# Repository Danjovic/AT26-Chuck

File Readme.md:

# AT-26 Chuck
This project allow the use of a Wii Nunchuck for playing games with Atari 2600 and other video-games with compatible joystick port (like ZX Spectrum w/ Kempston).

The heart of the circuit is a PIC microcontroller that converts I2C data from Wii Nunchuck. into pressing of switches on the Atari Joystick.

The device can be programmed into several modes of operation, with or without the accelerometers and auto-fire. The configuration is stored in EEPROM.

All components are through hole and the board can be easily built at home.

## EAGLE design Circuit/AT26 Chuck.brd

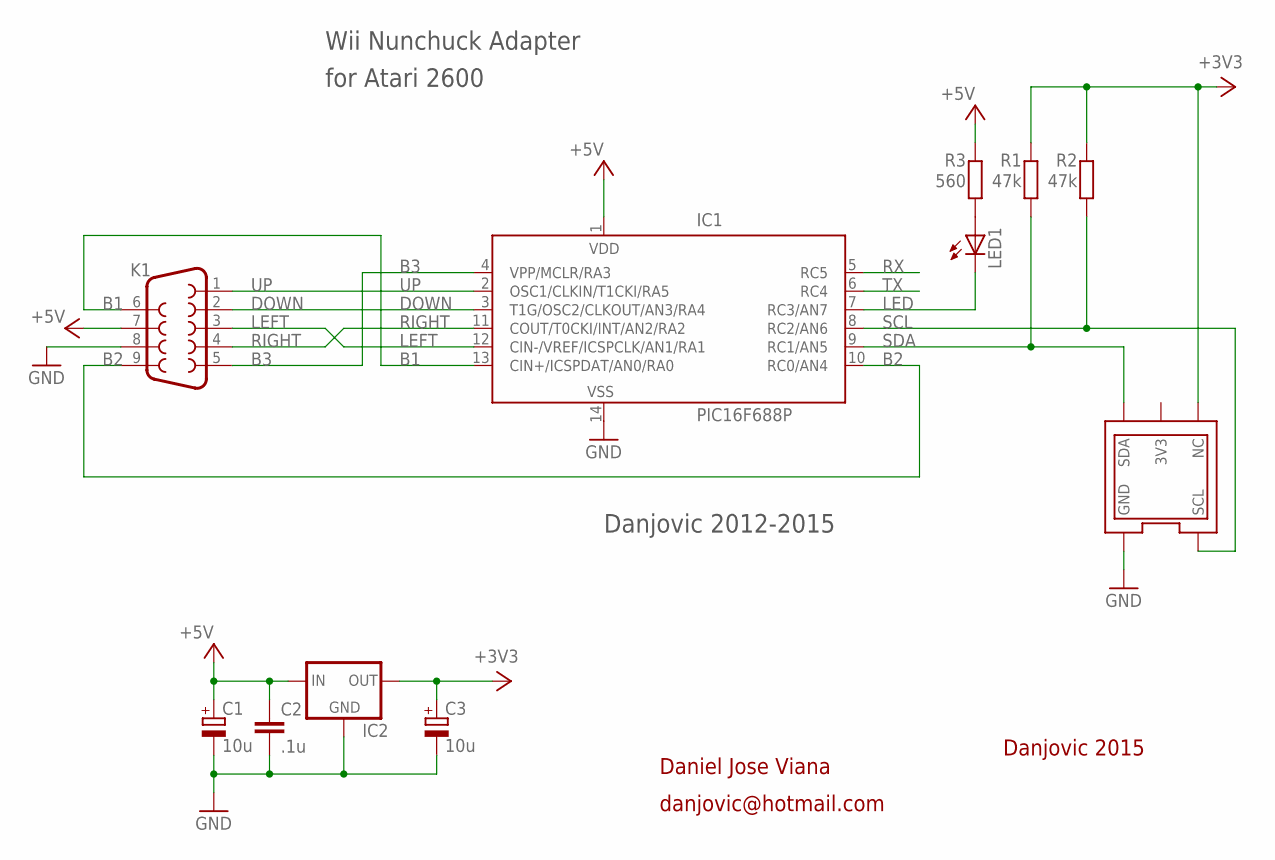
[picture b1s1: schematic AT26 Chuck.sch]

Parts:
C1, C3: 10u; E2,5-5
C2: .1u; C025-024X044L
IC1: PIC16F688P; DIL14
IC2: 78LXX78LXX_L; 78LXX_L
K1: F09D
LED1: LED3MM
R1, R2: 47k; 0204V
R3: 560; 0204V
U$1: NUNCHUCK; NUNCHUCK_SLOT

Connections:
+3V3: C3.+, IC2.OUT, R1.2, R2.2, U$1.NC
+5V: C1.+, C2.1, IC1.1 (VDD), IC2.IN, K1.7, R3.2
B1: IC1.13 (CIN+/ICSPDAT/AN0/RA0), K1.6
B2: IC1.10 (RC0/AN4), K1.9
B3: IC1.4 (VPP/MCLR/RA3), K1.5
DOWN: IC1.3 (T1G/OSC2/CLKOUT/AN3/RA4), K1.2
GND: C1.-, C2.2, C3.-, IC1.14 (VSS), IC2.GND, K1.8, U$1.GND
LED: IC1.7 (RC3/AN7), LED1.K (C)
LEFT: IC1.12 (CIN-/VREF/ICSPCLK/AN1/RA1), K1.3
unnamed: LED1.A, R3.1
RIGHT: IC1.11 (COUT/T0CKI/INT/AN2/RA2), K1.4
RX: IC1.5 (RC5)
SCL: IC1.8 (RC2/AN6), R2.1, U$1.SCL
SDA: IC1.9 (RC1/AN5), R1.1, U$1.SDA
TX: IC1.6 (RC4)
UP: IC1.2 (OSC1/CLKIN/T1CKI/RA5), K1.1

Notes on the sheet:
Danjovic 2015
Daniel Jose Viana
danjovic@hotmail.com
Danjovic 2012-2015
for Atari 2600
Wii Nunchuck Adapter

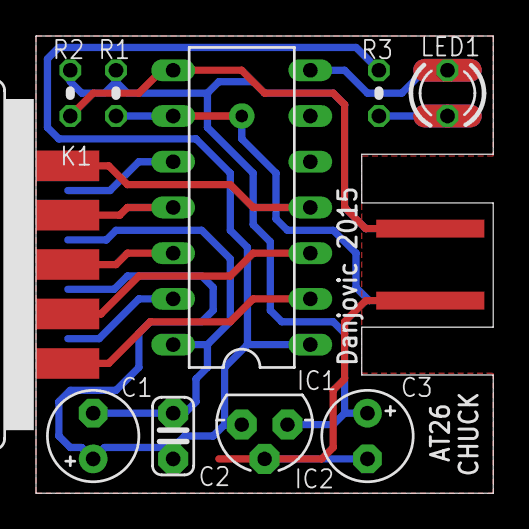
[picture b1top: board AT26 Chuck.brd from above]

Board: 2 copper layers, 25.4 x 25.4 mm, 11 parts (1 on the bottom side), 14 nets.

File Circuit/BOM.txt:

# AT26-Chuck Bill of Materials

IC1   - PIC16F688, DIP14 Package PIC microcontroller 4K Flash, 14 pins
IC2   - 78L33 Voltage Regulator, TO92 package
LED1  - 3mm LED, Yellow 3mm LED, Yellow
C1,C3 - 10uF/16V Electrolytic Capacitor, radial
C2    - 100nf Polyester/Ceramic capacitor
R1,R2 - 47K 1/4W Resistor, 1/4 Watt
R3    - 560 Ohms 1/4W Resistor, 1/4 Watt
K1    - DB-9 Female SUBD connector, 9 pins, female, pins for soldering

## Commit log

2015-11-28 :neckbeard: Added .gitattributes & .gitignore files
2015-11-28 Basic Release
2015-11-28 Added License files
2015-11-28 Excluded CAM files from gitignore
2015-11-28 Added Gerber Files
2016-06-30 Alternate Firmware, SNES to Atari Converter
    (still experimental)
2016-07-01 Alternate SNES-to-Atari firmware, working version
